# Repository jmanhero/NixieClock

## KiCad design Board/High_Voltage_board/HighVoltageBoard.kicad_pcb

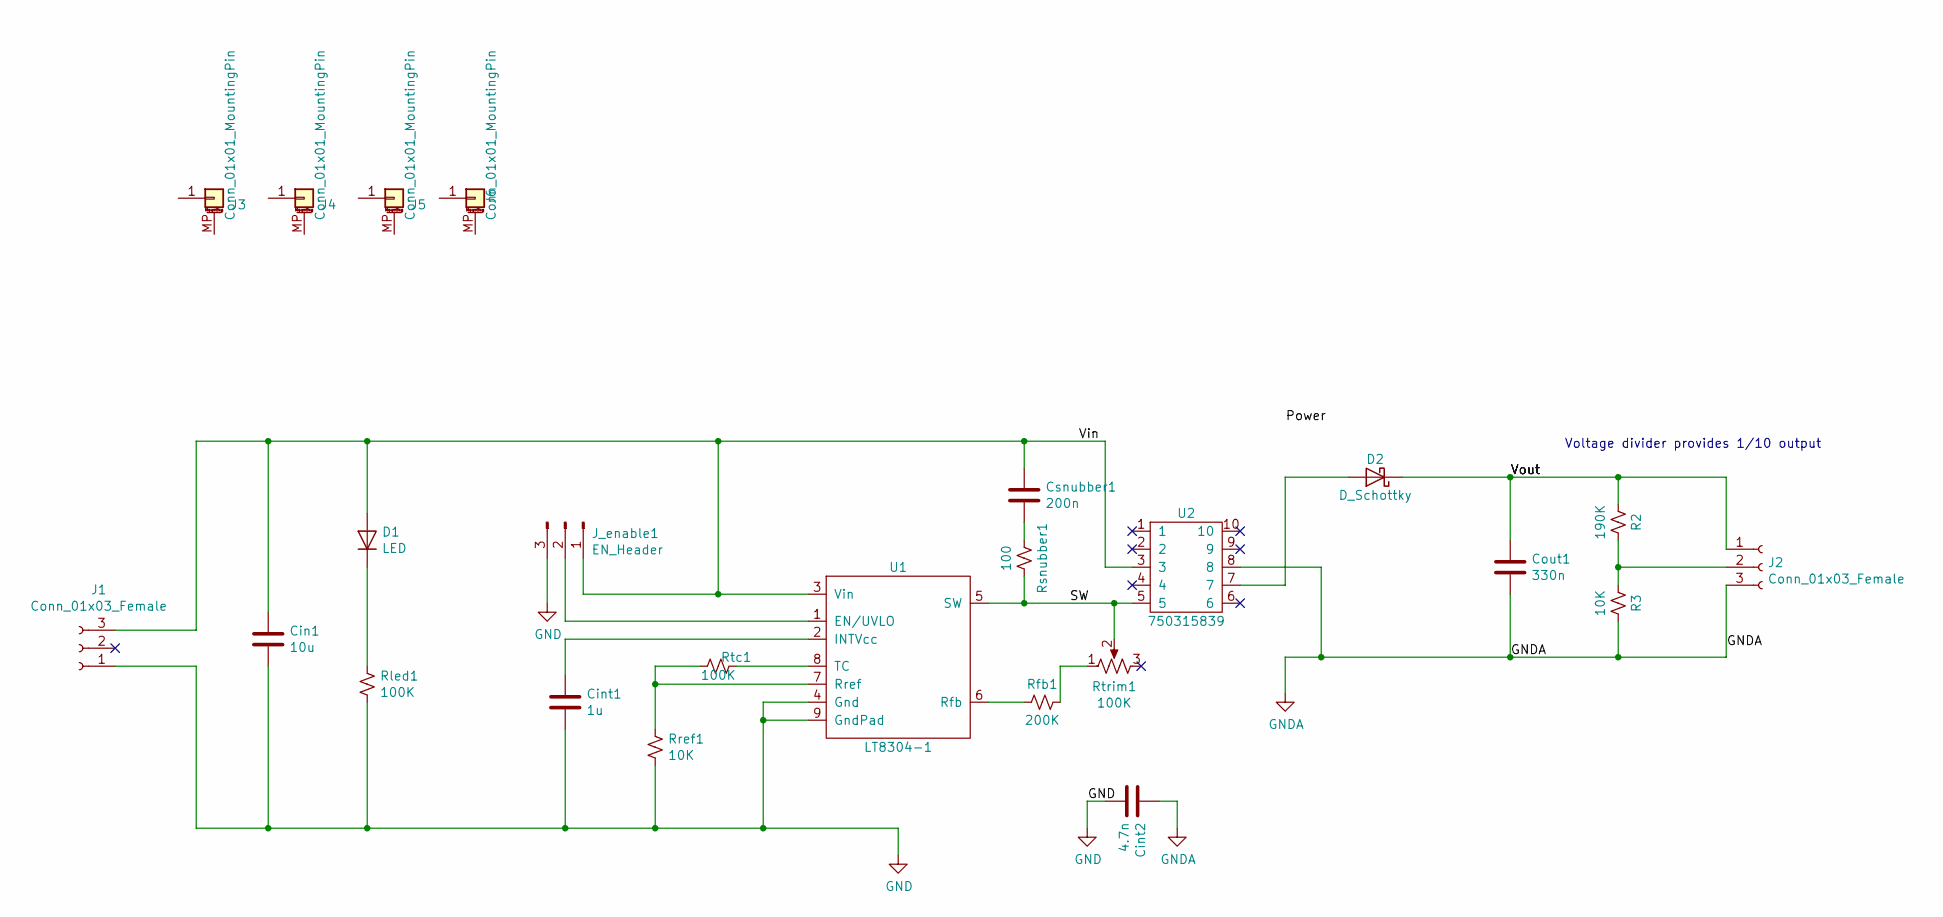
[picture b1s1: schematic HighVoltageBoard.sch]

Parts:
Cin1: 10u; C_0805_2012Metric_Pad1.15x1.40mm_HandSolder
Cint1: 1u; C_0805_2012Metric_Pad1.15x1.40mm_HandSolder
Cint2: 4.7n; C_0805_2012Metric_Pad1.15x1.40mm_HandSolder
Cout1: 330n; C_0805_2012Metric_Pad1.15x1.40mm_HandSolder
Csnubber1: 200n; C_0805_2012Metric_Pad1.15x1.40mm_HandSolder
D1: LED; D_0805_2012Metric_Pad1.15x1.40mm_HandSolder
D2: D_Schottky; D_PowerDI-123
J1, J2: Conn_01x03_Female; TerminalBlock_TE_282834-3_1x03_P2.54mm_Horizontal
J3, J4, J5, J6: Conn_01x01_MountingPin; MountingHole_2.7mm
J_enable1: EN_Header; FanPinHeader_1x03_P2.54mm_Vertical
R2: 190K; R_0805_2012Metric_Pad1.15x1.40mm_HandSolder
R3: 10K; R_0805_2012Metric_Pad1.15x1.40mm_HandSolder
Rfb1: 200K; R_0805_2012Metric_Pad1.15x1.40mm_HandSolder
Rled1: 100K; R_0805_2012Metric_Pad1.15x1.40mm_HandSolder
Rref1: 10K; R_0805_2012Metric_Pad1.15x1.40mm_HandSolder
Rsnubber1: 100; R_0805_2012Metric_Pad1.15x1.40mm_HandSolder
Rtc1: 100K; R_0805_2012Metric_Pad1.15x1.40mm_HandSolder
Rtrim1: 100K; Potentiometer_Vishay_TS53YJ_Vertical
U1: LT8304-1
U2: 750315839

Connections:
/SW: Rsnubber1.2, Rtrim1.2, U1.5 (SW), U2.5
/Vin: Cin1.1, Csnubber1.1, D1.2 (A), J1.3, J_enable1.1, U1.3 (Vin), U2.3; also elsewhere on the board
/Vout: Cout1.1, D2.1 (K), J2.1, R2.1
GND: Cin1.2, Cint1.2, Cint2.2, J1.1, J_enable1.3, Rled1.2, Rref1.1, U1.4 (Gnd), U1.9 (GndPad); also elsewhere on the board
GNDA: Cint2.1, Cout1.2, J2.3, R3.2, U2.8
unnamed: Cint1.1, U1.2 (INTVcc)
unnamed: Csnubber1.2, Rsnubber1.1
unnamed: D1.1 (K), Rled1.1
unnamed: D2.2 (A), U2.7
unnamed: J2.2, R2.2, R3.1
unnamed 15: J_enable1.2, U1.1 (EN/UVLO); also elsewhere on the board
unnamed: Rfb1.1, U1.6 (Rfb)
unnamed: Rfb1.2, Rtrim1.1
unnamed: Rref1.2, Rtc1.2, U1.7 (Rref)
unnamed: Rtc1.1, U1.8 (TC)

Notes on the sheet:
Voltage divider provides 1/10 output

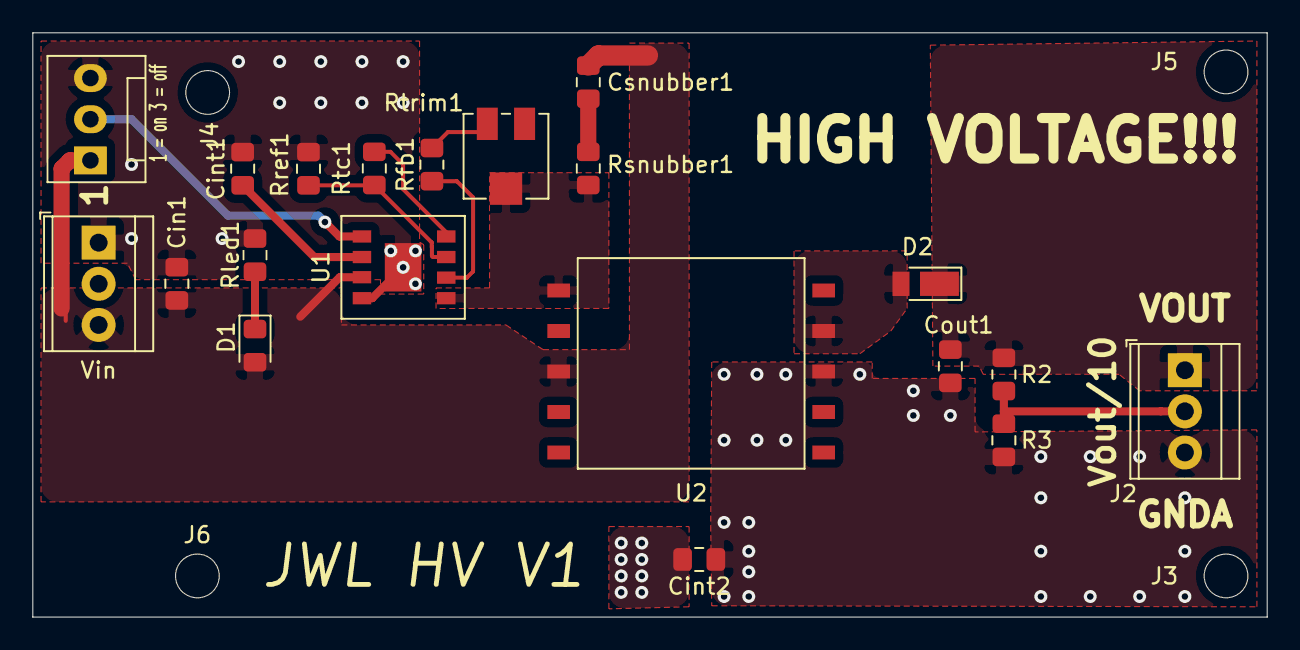
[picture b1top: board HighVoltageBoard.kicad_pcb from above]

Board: 2 copper layers, 76.2 x 36.1 mm, 24 parts (0 on the bottom side), 15 nets.

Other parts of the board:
1 = on 3 = off: EN_Header; FanPinHeader_1x03_P2.54mm_Vertical
Vin: Conn_01x03_Female; TerminalBlock_TE_282834-3_1x03_P2.54mm_Horizontal

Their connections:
/Vin: 1 = on 3 = off.1, Vin.3; also elsewhere on the board
GND: 1 = on 3 = off.3, Vin.1; also elsewhere on the board
unnamed 15: 1 = on 3 = off.2; also elsewhere on the board

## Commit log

2019-11-30 simulation done and working part selection is compete for the main power new thing to figure out is the current and voltage monitors
2019-12-31 updated the schematic and layed the board out
    all the schematic and board files are finalized
2019-12-31 updated board
    fixed courty yard issue on pin
2020-01-01 updated the bom
    created the bom off the schematic
